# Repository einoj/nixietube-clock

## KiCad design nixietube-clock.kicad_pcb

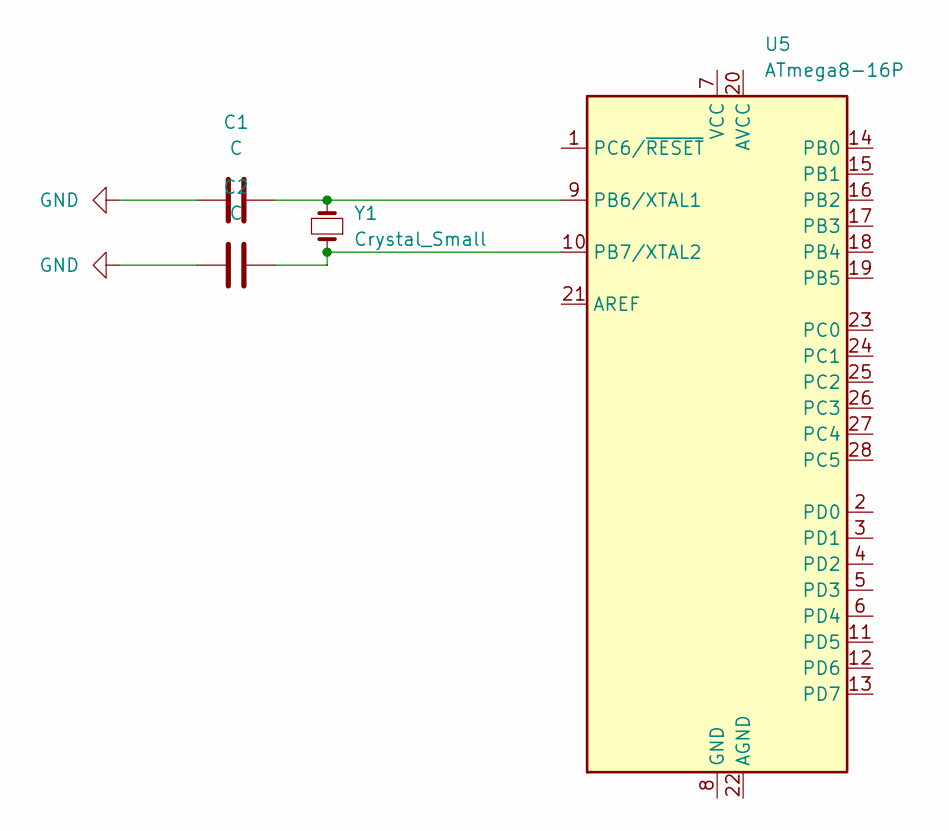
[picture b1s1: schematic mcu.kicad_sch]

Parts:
C1: C; C_0603_1608Metric
C2: C
U5: ATmega8-16P; DIP-28_W7.62mm
Y1: Crystal_Small; Crystal_AT310_D3.0mm_L10.0mm_Horizontal

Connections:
GND: C1.2, C2.2
unnamed: C1.1, U5.9 (PB6/XTAL1), Y1.2
unnamed: C2.1, U5.10 (PB7/XTAL2), Y1.1

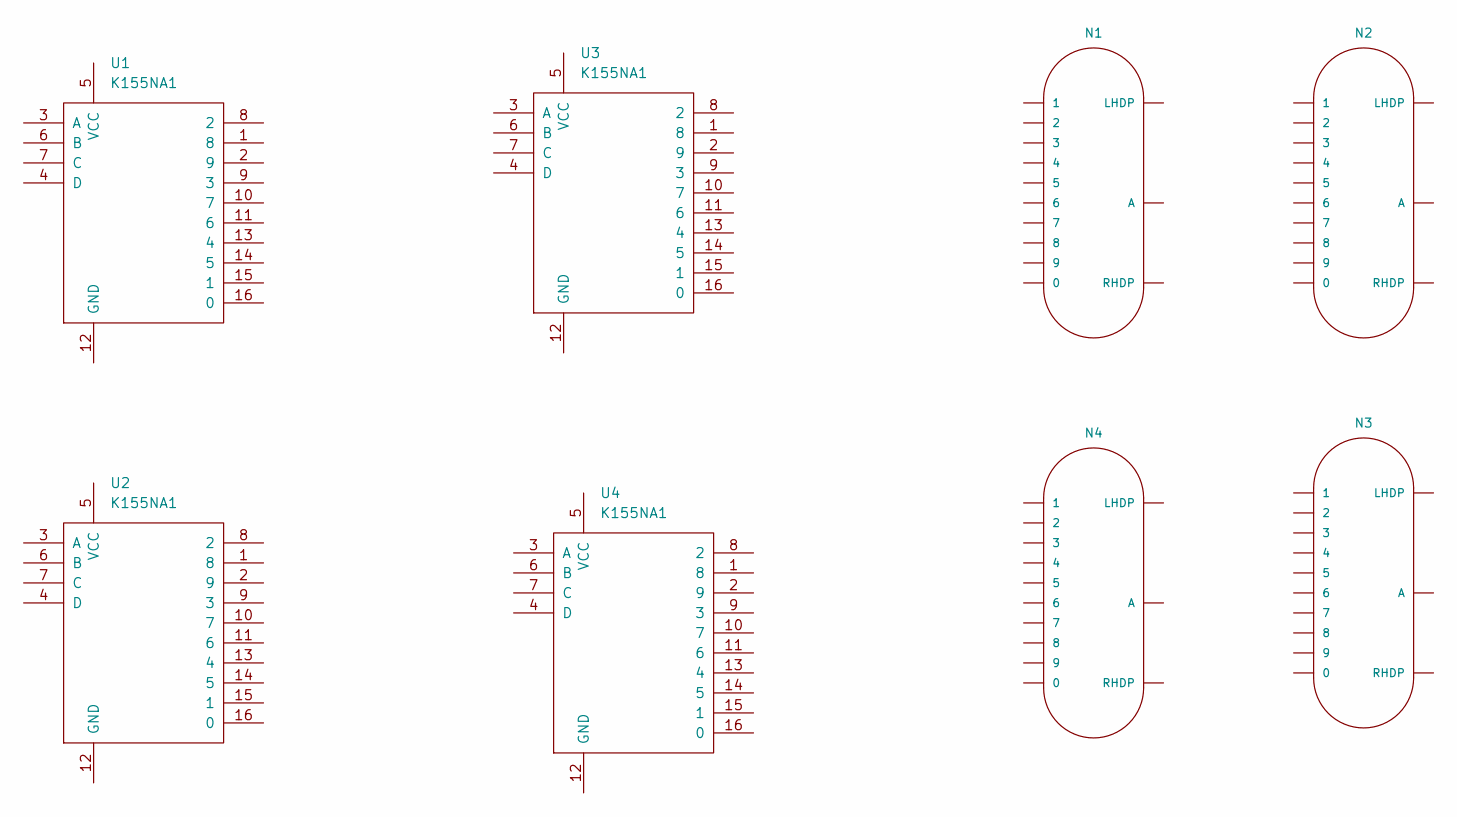
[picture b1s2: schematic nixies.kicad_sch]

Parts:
N1, N2, N3, N4: IN-14; nixies-us-IN-14
U1, U2, U3, U4: K155NA1; DIP-16_W7.62mm

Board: 2 copper layers, 11 parts (0 on the bottom side), 2 nets, no tracks yet.

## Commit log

2022-06-08 Add hiracical schematics and nixie symbols and footprints
    The hiracichal schematics added are:
    - power: DC-DC high voltage power converter
    - mcu: atmega8 microcontroller
    - input: user input, knobs and buttons
    - nixies: the in-14 nixie tubes and k155na1 nixie tube controllers
    Added symbols and footprints for the in-14 tubes and k155na1
2022-06-09 Convert legacy nixies.lib to new .kicad_sym format
2022-06-09 Add LM5156 flyback controller symbol
    And add it to the power sheet. This will be the controller for the 12 V
    to 170 V DC-DC converter.
